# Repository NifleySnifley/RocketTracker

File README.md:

`stable-launch` - this is the most stable and recently updated version - work here

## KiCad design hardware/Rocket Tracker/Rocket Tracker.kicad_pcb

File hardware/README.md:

# Tracker

## Features:

- ESP32 SoC with WiFi and Bluetooth for downloading flight logs

- 8Mb log storage (about 104 minutes of logging)

- 3 I2C peripheral ports

- SMA Antenna port (or wire antenna)

- Voltage regulator supporting up to 7 cell LiPo (1-2 cell reccomended)

## Power useage

| Part        | Current useage min (mA) | Current useage max |
| ----------- | ----------------------- | ------------------ |
| ESP32-WROOM | 160                     | 260                |
| RFM97CW     | 120                     | 140                |
| FGPMMOPA6H  | 20                      | 25                 |

## Assembly:

1. ESP32-WROOM module

2. GPS

3. Qwiic (JST-SH) connectors

4. LEDs and respective resistors

5. RFM97

6. Voltage regulator

7. Capacitors

8. Programming headers

9. Antenna or SMA connector

**Alternate (fast) procedure:**

1. Reflow all components on the top (ESP32, GPS, etc.)

2. Solder the bottom SMD components with paste and hot air gun

3. Hand solder the radio and THT components

## BOM:

| Ref         | Qnty | Value               | Cmp name            | Footprint                                                  | Description                                                                                                                                                                   | Vendor                                                                                              |
| ----------- | ---- | ------------------- | ------------------- | ---------------------------------------------------------- | ----------------------------------------------------------------------------------------------------------------------------------------------------------------------------- | --------------------------------------------------------------------------------------------------- |
| C1, C3,     | 2    | 10uF                | C_Small             | Capacitor_SMD:C_1210_3225Metric_Pad1.33x2.70mm_HandSolder  | Unpolarized capacitor, small symbol                                                                                                                                           | Digikey                                                                                             |
| C2,         | 1    | .1uF                | C_Small             | Capacitor_SMD:C_0603_1608Metric_Pad1.08x0.95mm_HandSolder  | Unpolarized capacitor, small symbol                                                                                                                                           | Digikey                                                                                             |
| D1, D2,     | 2    | LED                 | LED                 | LED_SMD:LED_0603_1608Metric_Pad1.05x0.95mm_HandSolder      | Light emitting diode                                                                                                                                                          | Digikey                                                                                             |
| J1,         | 1    | Conn_02x03_Odd_Even | Conn_02x03_Odd_Even | Connector_PinHeader_1.27mm:PinHeader_2x03_P1.27mm_Vertical | Generic connector, double row, 02x03, odd/even pin numbering scheme (row 1 odd numbers, row 2 even numbers), script generated (kicad-library-utils/schlib/autogen/connector/) | Digikey                                                                                             |
| J2,         | 1    | Conn_02x05_Odd_Even | Conn_02x05_Odd_Even | Connector_PinHeader_1.27mm:PinHeader_2x05_P1.27mm_Vertical | Generic connector, double row, 02x05, odd/even pin numbering scheme (row 1 odd numbers, row 2 even numbers), script generated (kicad-library-utils/schlib/autogen/connector/) | Digikey                                                                                             |
| J4,         | 1    | Conn_Coaxial        | Conn_Coaxial        | Connector_Coaxial:SMA_Amphenol_132289_EdgeMount            | coaxial connector (BNC, SMA, SMB, SMC, Cinch/RCA, LEMO, ...)                                                                                                                  | Digikey                                                                                             |
| J5,         | 1    | Conn_01x02          | Conn_01x02          | Connector_PinHeader_2.54mm:PinHeader_1x02_P2.54mm_Vertical | Generic connector, single row, 01x02, script generated (kicad-library-utils/schlib/autogen/connector/)                                                                        | Digikey                                                                                             |
| J6, J7, J8, | 3    | Conn_01x04          | Conn_01x04          | Parts:Connector_Qwiic_Vertical                             | Generic connector, single row, 01x04, script generated (kicad-library-utils/schlib/autogen/connector/)                                                                        | Digikey                                                                                             |
| R1, R2,     | 2    | R_Small             | R_Small             | Resistor_SMD:R_0603_1608Metric_Pad0.98x0.95mm_HandSolder   | Resistor, small symbol                                                                                                                                                        | Digikey                                                                                             |
| U1,         | 1    | ESP32-WROOM-32      | ESP32-WROOM-32      | RF_Module:ESP32-WROOM-32                                   | RF Module, ESP32-D0WDQ6 SoC, Wi-Fi 802.11b/g/n, Bluetooth, BLE, 32-bit, 2.7-3.6V, onboard antenna, SMD                                                                        | [SparkFun](https://www.sparkfun.com/products/17830)                                                 |
| U2,         | 1    | RFM97CW-915S2       | RFM97CW-915S2       | RF_Module:HOPERF_RFM9XW_SMD                                | Low power long range transceiver module, SPI and parallel interface, 915 MHz, spreading factor 6 to12, bandwith 7.8 to 500kHz, -111 to -139 dBm, SMD-16, DIP-16               | [SparkFun](https://www.sparkfun.com/products/18084)                                                 |
| U3,         | 1    | FGPMMOPA6H          | FGPMMOPA6H          | Parts:FGPMMOPA6H                                           | "Adafruit Ultimate MTK3333 GPS"                                                                                                                                               | Adafruit, [Cheap Source](https://www.tinyosshop.com/index.php?route=product/product&product_id=840) |
| U5,         | 1    | LD1117V33           | LD1117V33           | Package_TO_SOT_SMD:TO-252-2                                | 1.5A 35V Adjustable Linear Regulator, TO-220                                                                                                                                  | Digikey                                                                                             |
| U4,         | 1    | BMI160              | BMI160              | Package_LGA:Bosch_LGA-14_3x2.5mm_P0.5mm                    | Small, low power inertial measurement unit, LGA-14                                                                                                                            | Chip Shortage                                                                                       |
| R3, R4,     | 2    | 10k                 | R_Small             | Resistor_SMD:R_0603_1608Metric_Pad0.98x0.95mm_HandSolder   | Resistor, small symbol                                                                                                                                                        | Digikey                                                                                             |

# Tracker (BaseStationHAT)

## BOM:

| Ref     | Qnty | Value                        | Cmp name                 | Footprint                                                  | Description                                                                                                                                                                   | Vendor                                              |
| ------- | ---- | ---------------------------- | ------------------------ | ---------------------------------------------------------- | ----------------------------------------------------------------------------------------------------------------------------------------------------------------------------- | --------------------------------------------------- |
| AE1,    | 1    | Antenna_Chip                 | Antenna_Chip             | RF_Antenna:Pulse_W3011                                     | Ceramic chip antenna with pin for PCB trace                                                                                                                                   | Digikey                                             |
| BT1,    | 1    | Battery_Cell                 | Battery_Cell             | Battery:BatteryHolder_Keystone_3000_1x12mm                 | Single-cell battery                                                                                                                                                           | [SparkFun](https://www.sparkfun.com/products/10592) |
| C1,     | 1    | 3.3pF                        | C_Small                  | Capacitor_SMD:C_0402_1005Metric_Pad0.74x0.62mm_HandSolder  | Unpolarized capacitor, small symbol                                                                                                                                           | Digikey                                             |
| C2,     | 1    | .1uF                         | C_Small                  | Capacitor_SMD:C_0603_1608Metric_Pad1.08x0.95mm_HandSolder  | Unpolarized capacitor, small symbol                                                                                                                                           | Digikey                                             |
| C3,     | 1    | 10uF                         | C_Small                  | Capacitor_SMD:C_1210_3225Metric_Pad1.33x2.70mm_HandSolder  | Unpolarized capacitor, small symbol                                                                                                                                           | Digikey                                             |
| J1,     | 1    | Screw_Terminal_01x02         | Screw_Terminal_01x02     | TerminalBlock:TerminalBlock_bornier-2_P5.08mm              | Generic screw terminal, single row, 01x02, script generated (kicad-library-utils/schlib/autogen/connector/)                                                                   | Digikey                                             |
| J2, J4, | 2    | Conn_Coaxial                 | Conn_Coaxial             | CONREVSMA003:LINX_CONREVSMA003.062                         | coaxial connector (BNC, SMA, SMB, SMC, Cinch/RCA, LEMO, ...)                                                                                                                  | Digikey                                             |
| J3,     | 1    | 40HAT                        | OX40HAT                  | Connector_PinSocket_2.54mm:PinSocket_2x20_P2.54mm_Vertical | 20x2 (40 pin) female pin socket, 2.54mm pitch (Raspberry pi receptacle)                                                                                                       | Anny supplier                                       |
| J5,     | 1    | Conn_02x06_Counter_Clockwise | Conn_02x06_Odd_Even      | Connector_PinHeader_2.54mm:PinHeader_2x06_P2.54mm_Vertical | Generic connector, double row, 02x06, odd/even pin numbering scheme (row 1 odd numbers, row 2 even numbers), script generated (kicad-library-utils/schlib/autogen/connector/) | Digikey                                             |
| J6,     | 1    | Conn_01x10                   | Conn_01x10               | Connector_PinHeader_2.54mm:PinHeader_1x10_P2.54mm_Vertical | Generic connector, single row, 01x10, script generated (kicad-library-utils/schlib/autogen/connector/)                                                                        | Digikey                                             |
| J7, J8, | 2    | Conn_01x04                   | Conn_01x04               | Parts:Connector_Qwiic_Vertical                             | Generic connector, single row, 01x04, scrhttps://www.sparkfun.com/products/16766ipt generated (kicad-library-utils/schlib/autogen/connector/)                                 | [SparkFun]()                                        |
| JP1,    | 1    | Jumper_3_Bridged12           | Jumper_3_Bridged12       | Connector_PinHeader_2.54mm:PinHeader_1x03_P2.54mm_Vertical | Jumper, 3-pole, pins 1+2 closed/bridged                                                                                                                                       | Digikey                                             |
| JP2,    | 1    | SolderJumper_3_Open          | SolderJumper_3_Open      | Jumper:SolderJumper-3_P1.3mm_Open_Pad1.0x1.5mm             | Solder Jumper, 3-pole, open                                                                                                                                                   | N/A                                                 |
| JP3,    | 1    | SolderJumper_3_Bridged12     | SolderJumper_3_Bridged12 | Jumper:SolderJumper-3_P1.3mm_Bridged12_Pad1.0x1.5mm        | 3-pole Solder Jumper, pins 1+2 closed/bridged                                                                                                                                 | N/A                                                 |
| R1,     | 1    | 1k                           | R_Small                  | Resistor_SMD:R_0603_1608Metric_Pad0.98x0.95mm_HandSolder   | Resistor, small symbol                                                                                                                                                        | Digikey                                             |
| R2,     | 1    | 10k                          | R_Small                  | Resistor_SMD:R_0603_1608Metric_Pad0.98x0.95mm_HandSolder   | Resistor, small symbol                                                                                                                                                        | Digikey                                             |
| U1,     | 1    | RFM97CW-915S2                | RFM97CW-915S2            | RF_Module:HOPERF_RFM9XW_SMD                                | Low power long range transceiver module, SPI and parallel interface, 915 MHz, spreading factor 6 to12, bandwith 7.8 to 500kHz, -111 to -139 dBm, SMD-16, DIP-16               | [SparkFun](https://www.sparkfun.com/products/18084) |
| U2,     | 1    | ATtiny414-SS                 | ATtiny414-SS             | Package_SO:SOIC-14_3.9x8.7mm_P1.27mm                       | 20MHz, 4kB Flash, 256B SRAM, 128B EEPROM, SOIC-14                                                                                                                             | Digikey                                             |
| U3,     | 1    | RFM69HCW                     | RFM69HCW                 | RF_Module:HOPERF_RFM69HW                                   | Low power ISM Radio Transceiver Module, SPI interface, AES encryption, 434 or 915 MHz, up to 100mW, up to 300 kb/s, SMD-16, DIP-16                                            | [SparkFun](https://www.sparkfun.com/products/13909) |
| U4,     | 1    | SL871L                       | SL871L                   | Parts:SL871                                                |                                                                                                                                                                               | Digikey                                             |
| U5,     | 1    | MCP23008                     | MCP23008                 | Package_DIP:DIP-18_W7.62mm_LongPads                        |                                                                                                                                                                               | Digikey                                             |
| U6,     | 1    | LD1117V33                    | LD1117V33                | Package_TO_SOT_SMD:TO-252-2                                | 1.5A 35V Adjustable Linear Regulator, TO-220                                                                                                                                  | Digikey                                             |

## Features:

- **ATtiny414 PRU**:
  
  - ****Programmed with Pi's UART0
  
  - All IO pins broken out
  
  - I2C connected to Pi's I2C1
  
  - Jumper for selecting UPDI (program mode) and VCC pullup for reset pin

- **RFM6X and RFM9X radio connections**:
  
  - Seperate CS and DIO0 connections to Pi allowing simultaneous operation
    
    - 9X: CS = GPIO18, DIO0 = GPIO27
    
    - 6X: CS = GPIO17, DIO0 = GPIO22
  
  - Shared reset pin
  
  - Individual antenna connections
    
    - edge-mount SMA/RP-SMA footprints

- **Telit SL871(L) GPS**:
  
  - NMEA Serial connected to UART3
  
  - I2C connected to I2C0
  
  - PulseLarsen chip antenna
  
  - Coin cell RTC battery
  
  - All important IO connected:
    
    - FORCEON: GPIO25
    
    - ANT_SC: GPIO23
    
    - ANT_OC: GPIO24
    
    - RESET: GPIO16
      
      - Note: must be pulled high or floating to enable GPS

- **MCP23008 GPIO Expander**:
  
  - All IO and power rail broken out to an easily accesible location on the board
  
  - Interfaced with I2C1 and interrupt pin connected to Pi's GPIO6

- **Screw terminals and voltage regulator for powering the Pi**:
  
  - Connected directly to the Pi's 5v rail and the 3.3v voltage regulator
  
  - **WARNING**: No reverse polarity or overvoltage protection provided, use at your own risk, and double check before connecting!

## Assembly:

It's reccomended to use solder paste and a hot air gun to solder the SMD components 

1. GPS (if applicable)

2. GPS antenna

3. Voltage regulator

4. ATtiny PRU

5. All SMD passives (pullups, caps)

6. Qwiic (I2C) connectors

7. Radio modules

8. (RP)SMA connectors (if applicable)

9. GPIO expander

10. Pin headers

11. HAT socket

12. Screw terminals

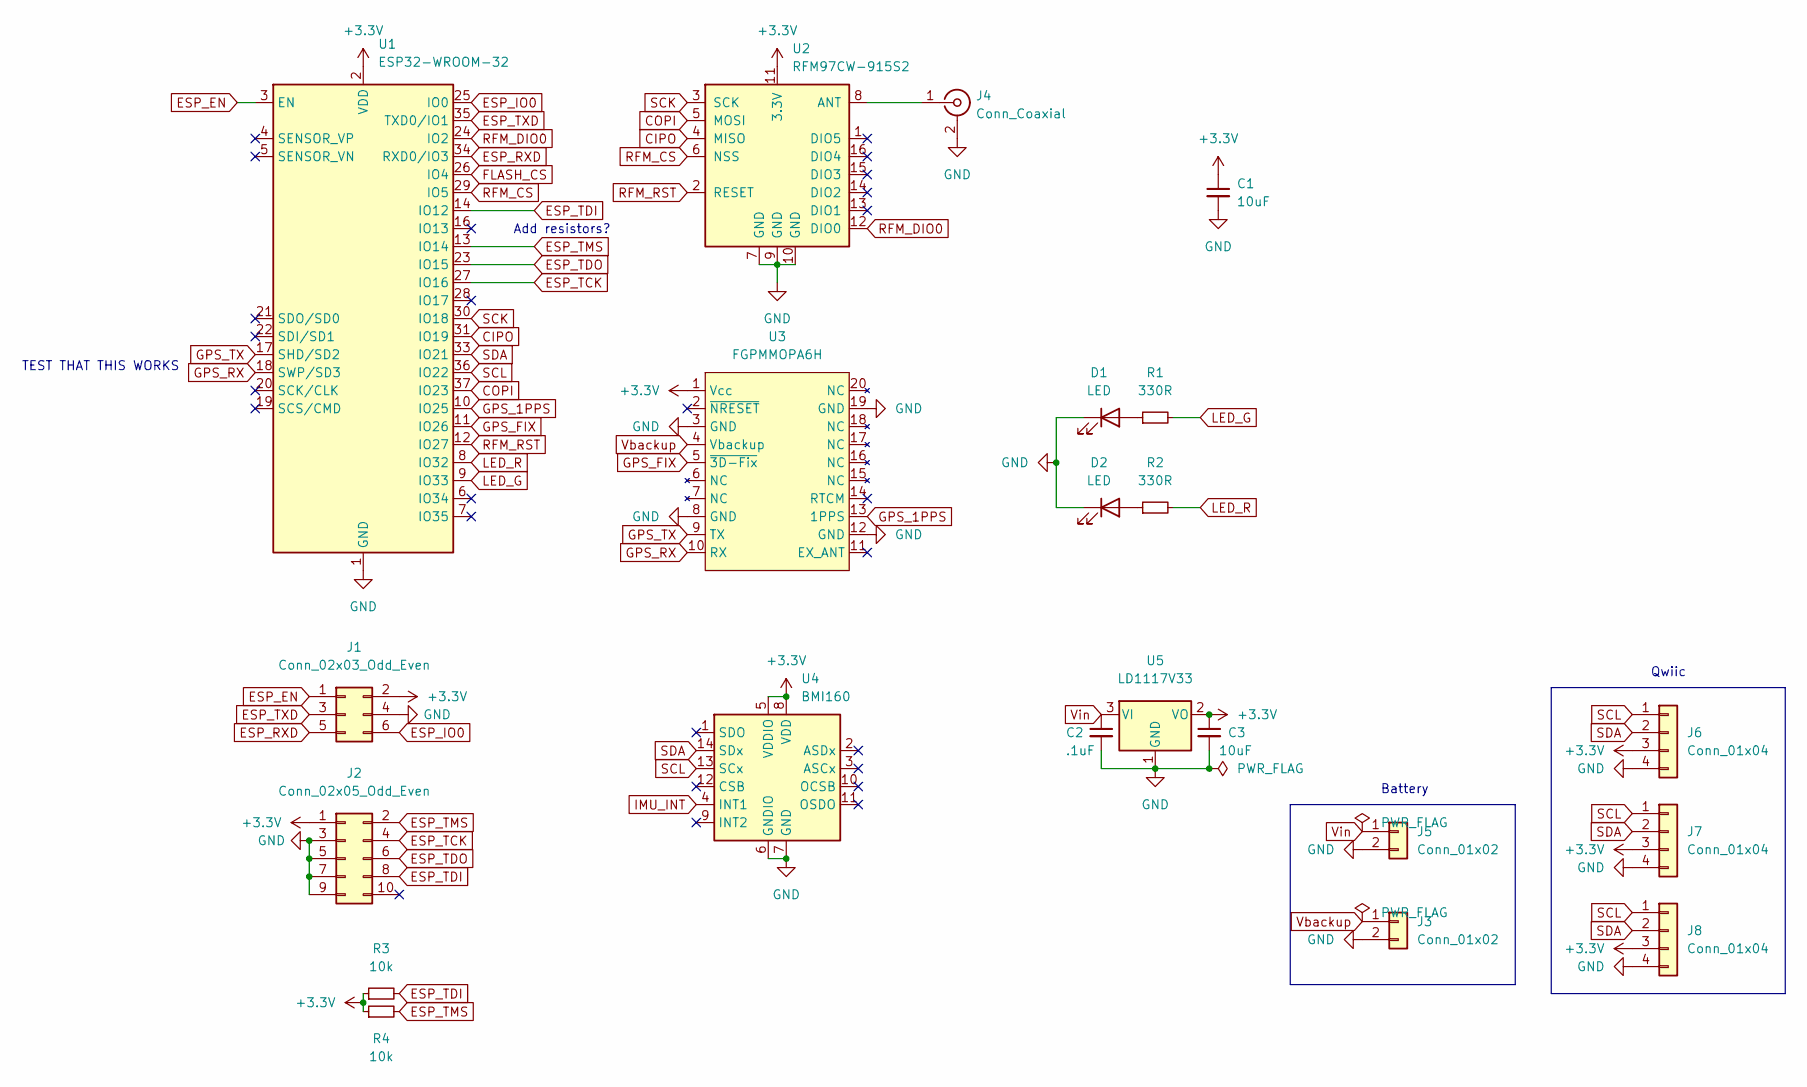
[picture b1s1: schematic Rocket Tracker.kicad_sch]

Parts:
C1, C3: 10uF; C_1210_3225Metric_Pad1.33x2.70mm_HandSolder
C2: .1uF; C_0603_1608Metric_Pad1.08x0.95mm_HandSolder
D1, D2: LED; LED_0603_1608Metric_Pad1.05x0.95mm_HandSolder
J1: Conn_02x03_Odd_Even; PinHeader_2x03_P1.27mm_Vertical
J2: Conn_02x05_Odd_Even; PinHeader_2x05_P1.27mm_Vertical
J3, J5: Conn_01x02; PinHeader_1x02_P2.54mm_Vertical
J4: Conn_Coaxial; LINX_CONREVSMA003.062
J6, J7, J8: Conn_01x04; Connector_Qwiic_Vertical
R1, R2: 330R; R_0603_1608Metric_Pad0.98x0.95mm_HandSolder
R3, R4: 10k; R_0603_1608Metric_Pad0.98x0.95mm_HandSolder
U1: ESP32-WROOM-32
U2: RFM97CW-915S2; HOPERF_RFM9XW_SMD
U3: FGPMMOPA6H
U4: BMI160; Bosch_LGA-14_3x2.5mm_P0.5mm
U5: LD1117V33; TO-252-2

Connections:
+3V3: C1.1, C3.1, J1.2, J2.1, J6.3, J7.3, J8.3, R3.1, R4.1, U1.2 (VDD), U2.11 (3.3V), U3.1 (Vcc), U4.5 (VDDIO), U4.8 (VDD), U5.2 (VO)
CIPO: U1.31 (IO19), U2.4 (MISO)
COPI: U1.37 (IO23), U2.5 (MOSI)
ESP_EN: J1.1, U1.3 (EN)
ESP_IO0: J1.6, U1.25 (IO0)
ESP_RXD: J1.5, U1.34 (RXD0/IO3)
ESP_TCK: J2.4, U1.27 (IO16)
ESP_TDI: J2.8, R3.2, U1.14 (IO12)
ESP_TDO: J2.6, U1.23 (IO15)
ESP_TMS: J2.2, R4.2, U1.13 (IO14)
ESP_TXD: J1.3, U1.35 (TXD0/IO1)
FLASH_CS: U1.26 (IO4)
GND: C1.2, C2.2, C3.2, D1.1 (K), D2.1 (K), J1.4, J2.3, J2.5, J2.7, J2.9, J3.2, J4.2 (Ext), J5.2, J6.4, J7.4, J8.4, U1.1 (GND), U1.15 (GND), U1.38 (GND), U1.39 (GND), U2.7 (GND), U2.9 (GND), U2.10 (GND), U3.3 (GND), U3.8 (GND), U3.12 (GND), U3.19 (GND), U4.6 (GNDIO), U4.7 (GND), U5.1 (GND)
GPS_1PPS: U1.10 (IO25), U3.13 (1PPS)
GPS_FIX: U1.11 (IO26), U3.5 (~3D-Fix)
GPS_RX: U1.18 (SWP/SD3), U3.10 (RX)
GPS_TX: U1.17 (SHD/SD2), U3.9 (TX)
IMU_INT: U4.4 (INT1)
LED_G: R1.2, U1.9 (IO33)
LED_R: R2.2, U1.8 (IO32)
unnamed: D1.2 (A), R1.1
unnamed: D2.2 (A), R2.1
unnamed: J4.1 (In), U2.8 (ANT)
RFM_CS: U1.29 (IO5), U2.6 (NSS)
RFM_DIO0: U1.24 (IO2), U2.12 (DIO0)
RFM_RST: U1.12 (IO27), U2.2 (RESET)
SCK: U1.30 (IO18), U2.3 (SCK)
SCL: J6.1, J7.1, J8.1, U1.36 (IO22), U4.13 (SCx)
SDA: J6.2, J7.2, J8.2, U1.33 (IO21), U4.14 (SDx)
Vbackup: J3.1, U3.4 (Vbackup)
Vin: C2.1, J5.1, U5.3 (VI)

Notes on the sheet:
TEST THAT THIS WORKS
Battery
Add resistors?
Qwiic

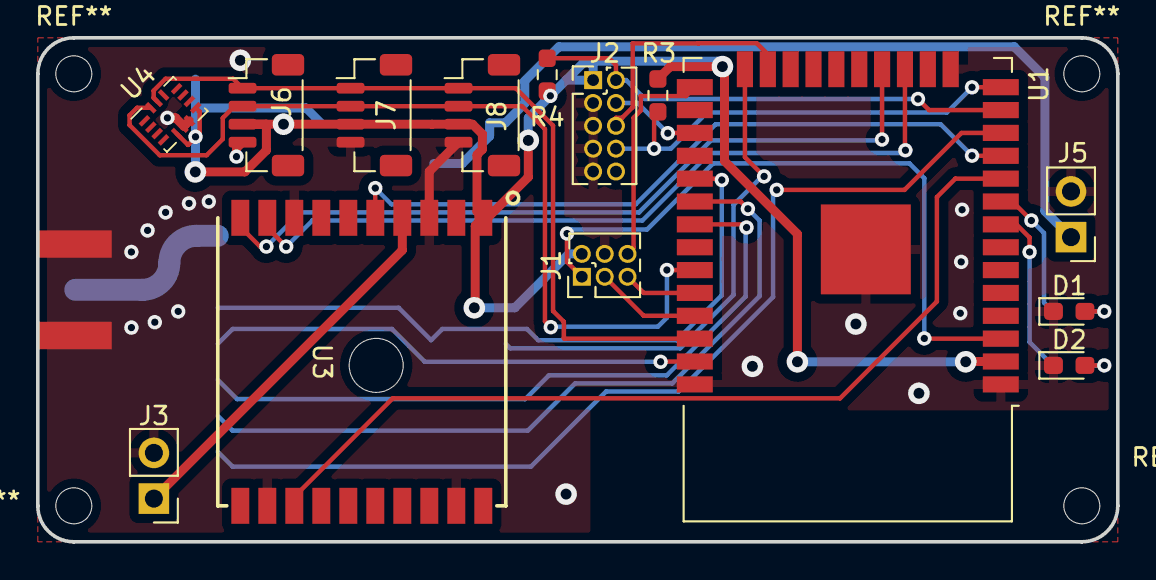
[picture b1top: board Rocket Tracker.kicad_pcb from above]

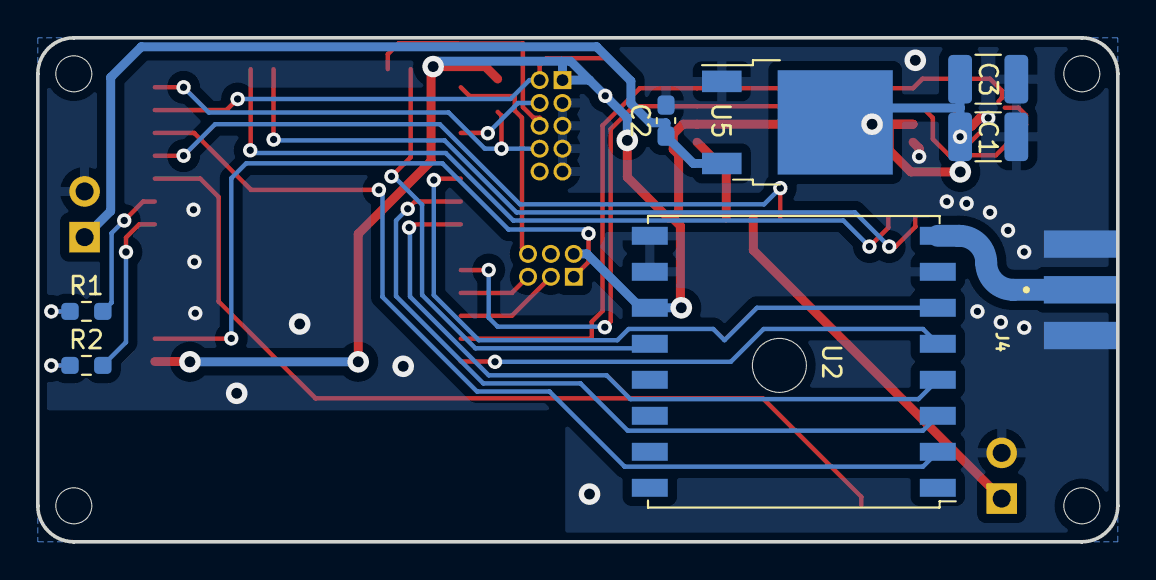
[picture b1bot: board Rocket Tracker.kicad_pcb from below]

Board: 2 copper layers, 60.0 x 28.0 mm, 22 parts (8 on the bottom side), 29 nets.

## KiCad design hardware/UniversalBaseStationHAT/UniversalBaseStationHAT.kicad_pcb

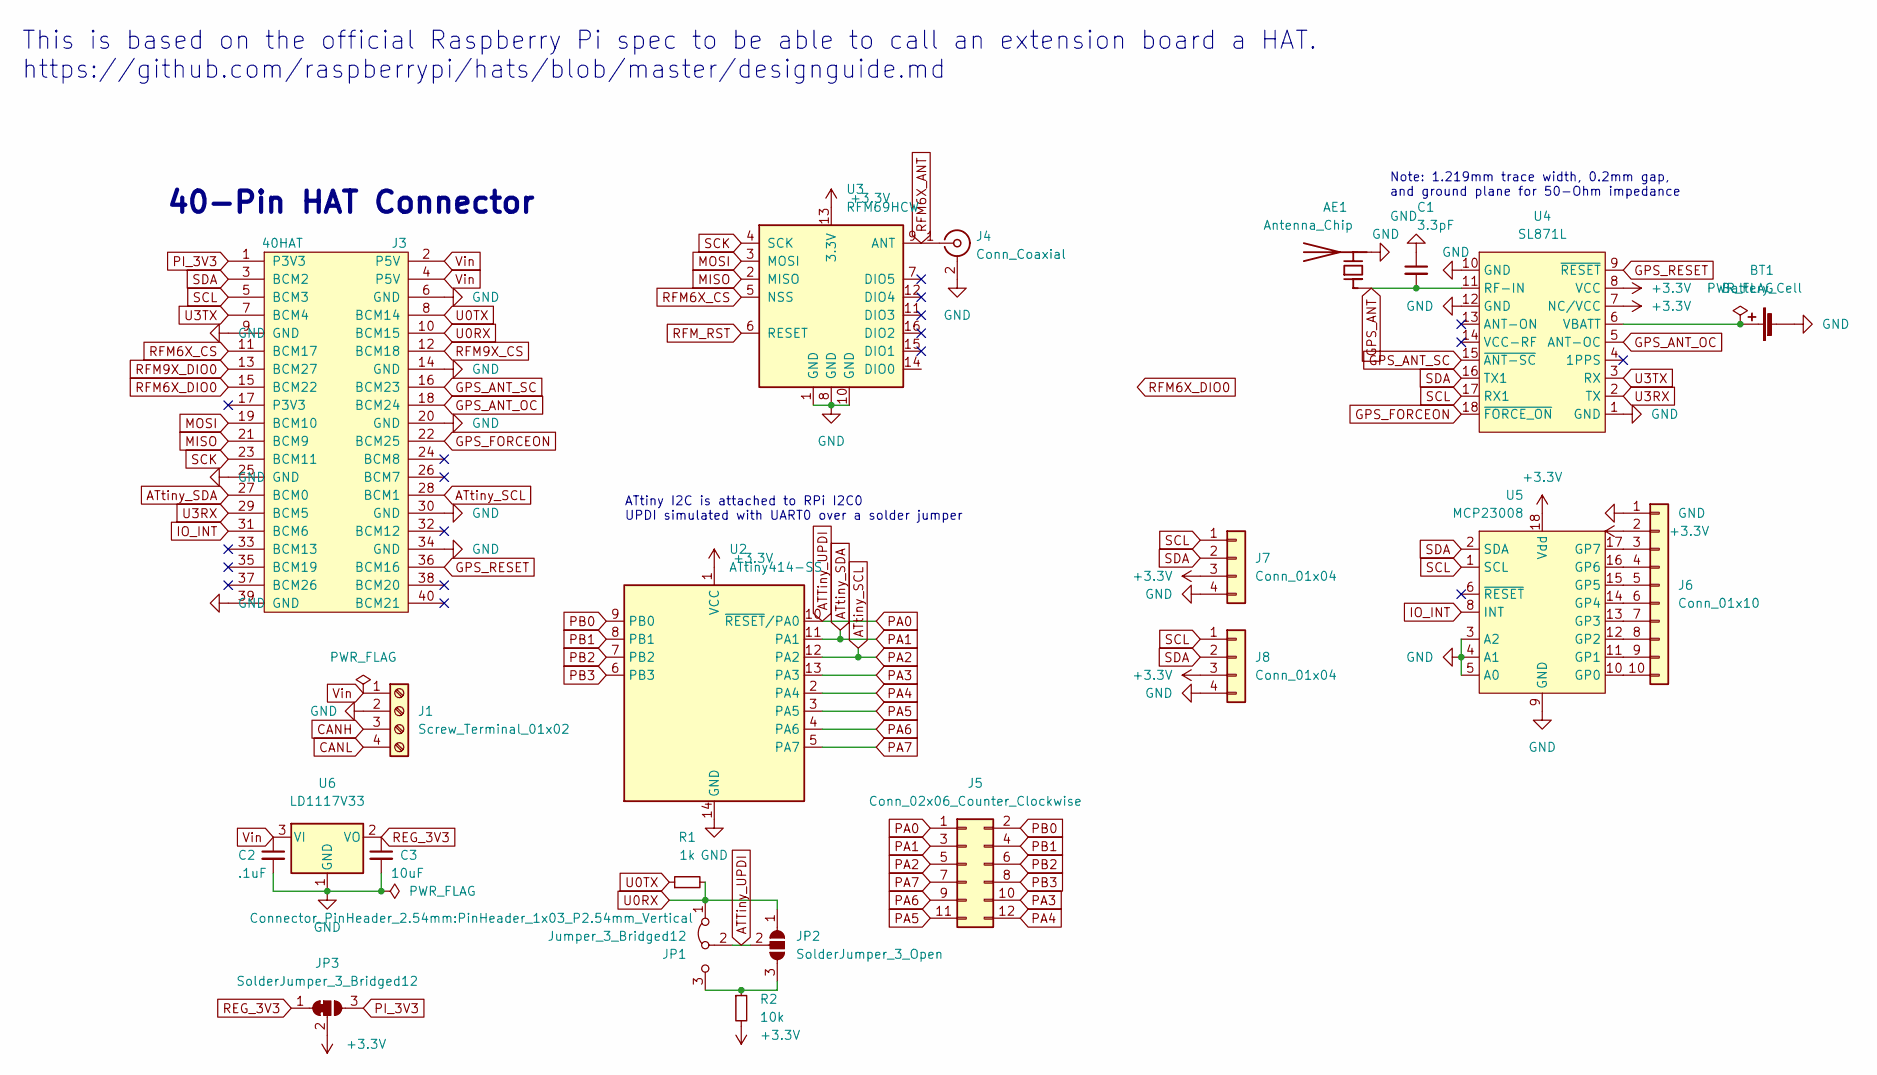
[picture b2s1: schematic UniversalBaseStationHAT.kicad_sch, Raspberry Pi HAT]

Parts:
AE1: Antenna_Chip; Pulse_W3011
BT1: Battery_Cell; BatteryHolder_Keystone_3000_1x12mm
C1: 3.3pF; C_0402_1005Metric_Pad0.74x0.62mm_HandSolder
C2: .1uF; C_0603_1608Metric_Pad1.08x0.95mm_HandSolder
C3: 10uF; C_1210_3225Metric_Pad1.33x2.70mm_HandSolder
J1: Screw_Terminal_01x02; TerminalBlock_bornier-4_P5.08mm
J3: 40HAT; PinSocket_2x20_P2.54mm_Vertical
J4: Conn_Coaxial; LINX_CONREVSMA003.062
J5: Conn_02x06_Counter_Clockwise; PinHeader_2x06_P2.54mm_Vertical
J6: Conn_01x10; PinHeader_1x10_P2.54mm_Vertical
J7, J8: Conn_01x04; Connector_Qwiic_Vertical
JP1: Jumper_3_Bridged12; PinHeader_1x03_P2.54mm_Vertical
JP2: SolderJumper_3_Open; SolderJumper-3_P1.3mm_Open_Pad1.0x1.5mm
JP3: SolderJumper_3_Bridged12; SolderJumper-3_P1.3mm_Bridged12_Pad1.0x1.5mm
R1: 1k; R_0603_1608Metric_Pad0.98x0.95mm_HandSolder
R2: 10k; R_0603_1608Metric_Pad0.98x0.95mm_HandSolder
U2: ATtiny414-SS; SOIC-14_3.9x8.7mm_P1.27mm
U3: RFM69HCW; HOPERF_RFM69HW
U4: SL871L; SL871
U5: MCP23008; DIP-18_W7.62mm_LongPads
U6: LD1117V33; TO-252-2

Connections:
+3V3: J6.2, J7.3, J8.3, JP3.2 (C), R2.2, U2.1 (VCC), U3.13 (3.3V), U4.7 (NC/VCC), U4.8 (VCC), U5.18 (Vdd)
ATTiny_UPDI: J5.1, JP1.2 (C), JP2.2 (C), U2.10 (~RESET/PA0)
ATtiny_SCL: J3.28 (BCM1), J5.5, U2.12 (PA2)
ATtiny_SDA: J3.27 (BCM0), J5.3, U2.11 (PA1)
CANH: J1.3
CANL: J1.4
GND: AE1.2 (PCB_Trace), BT1.2 (-), C1.1, C2.2, C3.2, J1.2, J3.6 (GND), J3.9 (GND), J3.14 (GND), J3.20 (GND), J3.25 (GND), J3.30 (GND), J3.34 (GND), J3.39 (GND), J4.2 (Ext), J6.1, J7.4, J8.4, U2.14 (GND), U3.1 (GND), U3.8 (GND), U3.10 (GND), U4.1 (GND), U4.10 (GND), U4.12 (GND), U5.3 (A2), U5.4 (A1), U5.5 (A0), U5.9 (GND), U6.1 (GND)
GPS_ANT: AE1.1 (FEED), C1.2, U4.11 (RF-IN)
GPS_ANT_OC: J3.18 (BCM24), U4.5 (ANT-OC)
GPS_ANT_SC: J3.16 (BCM23), U4.15 (~ANT-SC)
GPS_FORCEON: J3.22 (BCM25), U4.18 (~FORCE_ON)
GPS_RESET: J3.36 (BCM16), U4.9 (~RESET)
IO_INT: J3.31 (BCM6), U5.8 (INT)
MISO: J3.21 (BCM9), U3.2 (MISO)
MOSI: J3.19 (BCM10), U3.3 (MOSI)
unnamed: BT1.1 (+), U4.6 (VBATT)
unnamed: J6.3, U5.17 (GP7)
unnamed: J6.4, U5.16 (GP6)
unnamed: J6.5, U5.15 (GP5)
unnamed: J6.6, U5.14 (GP4)
unnamed: J6.7, U5.13 (GP3)
unnamed: J6.8, U5.12 (GP2)
unnamed: J6.9, U5.11 (GP1)
unnamed: J6.10, U5.10 (GP0)
unnamed: JP1.3 (B), JP2.3 (B), R2.1
PA3: J5.10, U2.13 (PA3)
PA4: J5.12, U2.2 (PA4)
PA5: J5.11, U2.3 (PA5)
PA6: J5.9, U2.4 (PA6)
PA7: J5.7, U2.5 (PA7)
PB0: J5.2, U2.9 (PB0)
PB1: J5.4, U2.8 (PB1)
PB2: J5.6, U2.7 (PB2)
PB3: J5.8, U2.6 (PB3)
PI_3V3: J3.1 (P3V3), JP3.3 (B)
REG_3V3: C3.1, JP3.1 (A), U6.2 (VO)
RFM6X_ANT: J4.1 (In), U3.9 (ANT)
RFM6X_CS: J3.11 (BCM17), U3.5 (NSS)
RFM6X_DIO0: J3.15 (BCM22)
RFM9X_CS: J3.12 (BCM18)
RFM9X_DIO0: J3.13 (BCM27)
RFM_RST: U3.6 (RESET)
SCK: J3.23 (BCM11), U3.4 (SCK)
SCL: J3.5 (BCM3), J7.1, J8.1, U4.17 (RX1), U5.1 (SCL)
SDA: J3.3 (BCM2), J7.2, J8.2, U4.16 (TX1), U5.2 (SDA)
U0RX: J3.10 (BCM15), JP1.1 (A), JP2.1 (A), R1.2
U0TX: J3.8 (BCM14), R1.1
U3RX: J3.29 (BCM5), U4.2 (TX)
U3TX: J3.7 (BCM4), U4.3 (RX)
Vin: C2.1, J1.1, J3.2 (P5V), J3.4 (P5V), U6.3 (VI)

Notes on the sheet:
This is based on the official Raspberry Pi spec to be able to call an extension board a HAT. https://github.com/raspberrypi/hats/blob/master/designguide.md
40-Pin HAT Connector
Note: 1.219mm trace width, 0.2mm gap, and ground plane for 50-Ohm impedance
ATtiny I2C is attached to RPi I2C0 UPDI simulated with UART0 over a solder jumper

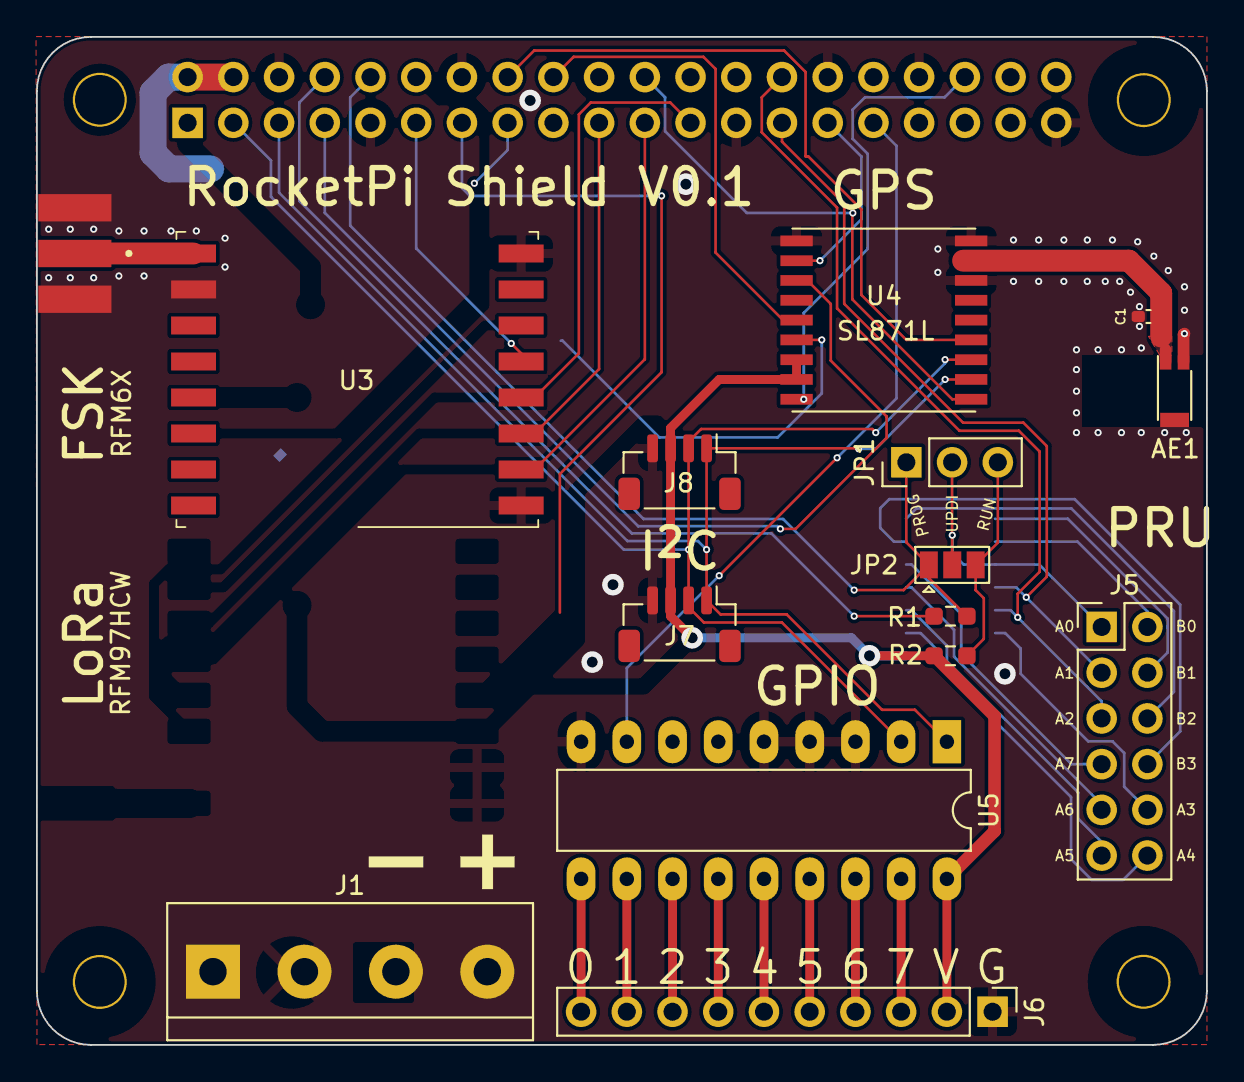
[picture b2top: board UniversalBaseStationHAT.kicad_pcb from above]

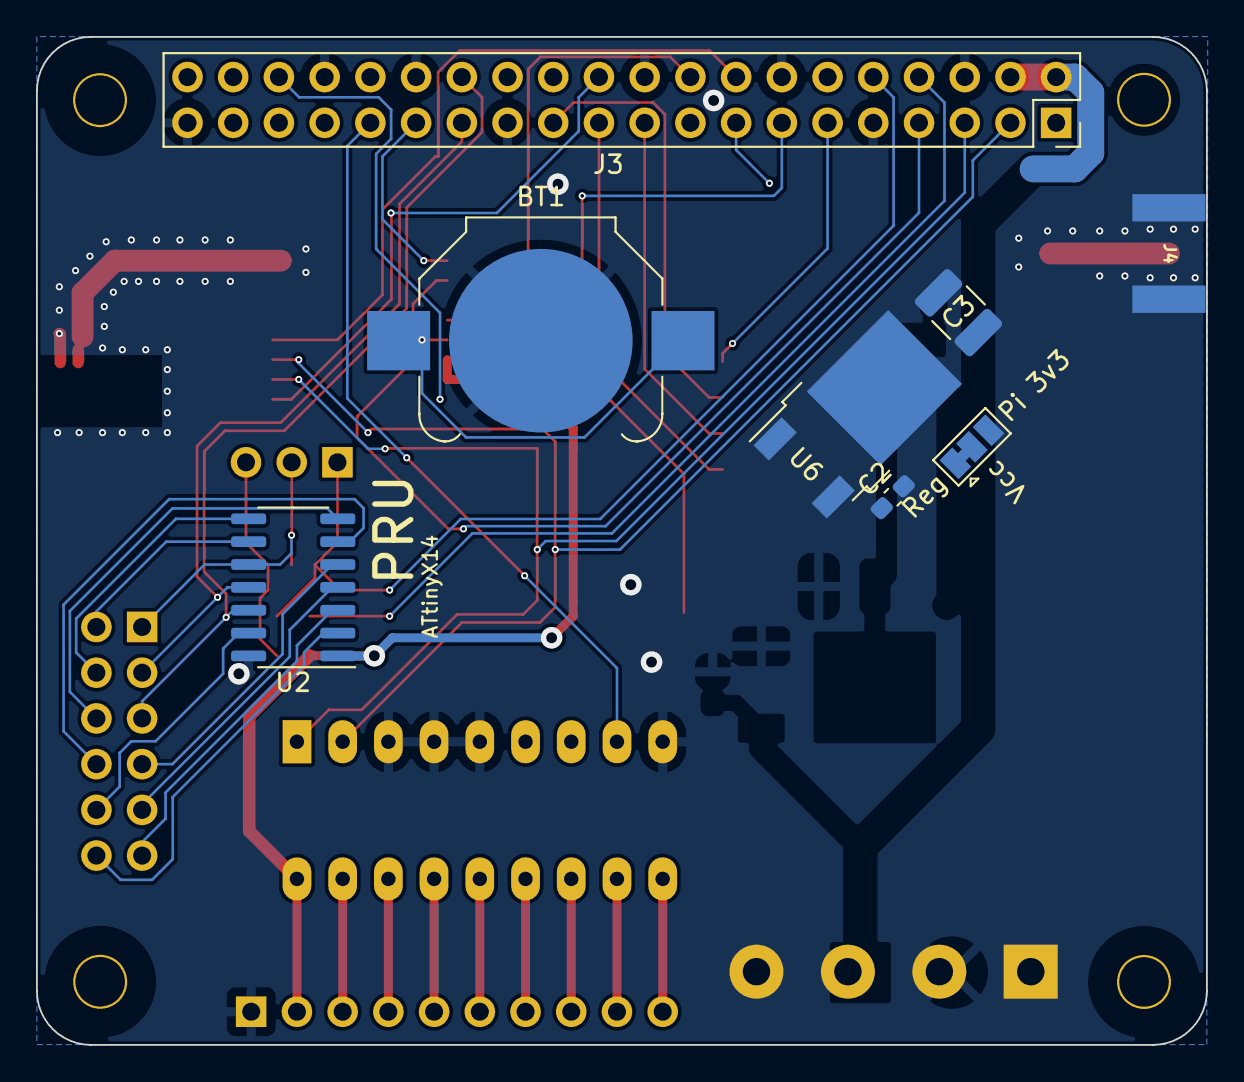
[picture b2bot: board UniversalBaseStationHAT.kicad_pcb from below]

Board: 2 copper layers, 65.0 x 56.0 mm, 26 parts (7 on the bottom side), 44 nets.

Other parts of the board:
H1, H2, H3, H4: 3mm_Mounting_Hole; NPTH_3mm_ID

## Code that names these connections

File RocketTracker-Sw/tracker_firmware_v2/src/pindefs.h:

// Pinout for U12 (ESP32-S3-WROOM-1)
#define PIN_EXP1 (gpio_num_t) 4
#define PIN_EXP2 (gpio_num_t) 5
#define PIN_EXP3 (gpio_num_t) 6
#define PIN_EXP4 (gpio_num_t) 7
#define PIN_LED_G (gpio_num_t) 15
#define PIN_LED_R (gpio_num_t) 16
#define PIN_GPS_SDI (gpio_num_t) 17
#define PIN_GPS_SDO (gpio_num_t) 18
#define PIN_USB_N (gpio_num_t) 19
#define PIN_USB_P (gpio_num_t) 20
#define PIN_ADXL_INT1 (gpio_num_t) 3
#define PIN_ADXL_CS (gpio_num_t) 9
#define PIN_LPS_CS (gpio_num_t) 10
#define PIN_MOSI (gpio_num_t) 11
#define PIN_SCK (gpio_num_t) 12
#define PIN_MISO (gpio_num_t) 13
#define PIN_LIS3MDL_CS (gpio_num_t) 14
#define PIN_LSM6DSM_CS (gpio_num_t) 21
#define PIN_ESP_BOOT (gpio_num_t) 0
#define PIN_RFM_RST (gpio_num_t) 35
#define PIN_RFM_D0 (gpio_num_t) 36
#define PIN_RFM_CS (gpio_num_t) 37
#define PIN_FLASH_CS (gpio_num_t) 38
#define PIN_TL_SCK (gpio_num_t) 39
#define PIN_TL_MOSI (gpio_num_t) 40
#define PIN_TL_MISO (gpio_num_t) 41
// #define PIN_NETNU12NRXD0 RXD0
// #define PIN_NETNU12NTXD0 TXD0
#define PIN_SCL (gpio_num_t) 2
#define PIN_SDA (gpio_num_t) 1

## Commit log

2022-06-29 Working cross-compilation and deployment to a Pi 4B
2022-06-29 Oopsie, restructured
2022-06-30 Basic compass support, its terrible though
2022-06-30 Configuration file, indev auto-calibration
2022-06-30 Fixed compass spinning, better GPS readout
2022-06-30 Improved compass rendering
2022-07-01 Working calibration, indev IMU
2022-07-01 Improved IMU reading
2022-07-19 Add template for tracker firmware
2022-07-20 Switched to PlatformIO and added protobufs
2022-07-21 Add more sophisticated transmission of data
2022-07-24 Tracker sending to seeker script with RFM97
2022-07-24 Added script to test radio receiving on seeker
2022-07-24 Transmission + reception seq. w/ modified RadioLib
2022-07-24 Modified test script with ack
2022-07-26 Better working radio transmissions
2022-07-26 Better receiver script
2022-07-27 Custom driver working for transmitting
2022-07-29 Fully operational driver
2022-07-30 Proper sending and configuration
2022-07-30 Copy files to redo seeker backend
2022-07-31 Fixed protobuf compilation and cleaned backend
2022-07-31 Template for frontend added and setup dev. env.
2022-07-31 Added font awesome icons
2022-08-01 Created (problably) worlds worst UI panel layout..
2022-08-04 WIP Adapters (traits) and README TODOs
2022-08-05 Added tungstenite websocket boilerplate.
2022-08-05 Basic amenities for event relaying
2022-08-06 Added map boilerplate, maptiler
2022-08-06 Satellite maps (basic)
2022-08-06 Improved adjustable grid layout
2022-08-07 Grid fixes, Websockets, etc.
2022-08-13 Added offline proxy
2022-08-13 JS Changes
2022-08-13 All fixed up (aside from the cache)
2022-08-14 Basic REST API (no functionality)
2022-08-22 WIP everything, did some work on backend
2023-04-13 Woah there! Started everything over. Added PCBs.
2023-04-13 I'm dumb, made PCBs submod and added SW dir
2023-07-30 Stuff, commit because commit
2023-08-16 Basic firmware for testing receiver, protocol infrastructure, forgot to commit
2023-08-18 Protocol things, DMA based asyncrhonous radio driver upgrades.
2023-08-19 Basic TinyUSB CDC ports, reset, etc.
2023-08-20 Emulated NMEA GPS for received messages, fixed driver
2023-08-21 Radio configuration via NMEA custom messages
2023-08-21 Minimal but "feature-complete" receiver firmware. Needs more extensive testing
2023-08-22 Remove debug messages from receiver firmware VGPS
2023-08-23 Working (basic) GPS tracking firmware!
2023-08-23 Restructure receiver for shared comms, radio rx status
2023-08-27 More work on stuff, PC software mostly
2023-08-27 Fix protobufs
2023-08-27 Escaping for raw message tx/rx
2023-08-28 Fixes for configuration of receiver w/ NMEA. No more CR config
2023-08-28 Operational GPS display on map!
2023-08-28 Builds with pyinstaller
2023-09-01 Stuff works?!?!?!
2023-09-01 Major additions to software, tweaked receiver
2023-09-01 Log analysis for basestation software
2023-09-01 Fixed proxy for Windows and requirements.txt
2023-09-05 Software improvements, bugfixes
2023-09-06 CRC check in framemanager for extra safety
2023-09-06 Fixes for CRC
2023-09-06 CRC supporting tracker firmware
2023-09-07 Barometric altitude in tracker firmware from LPS25
2023-09-07 Altitude graphs!
2023-09-07 Overall, software works! Could use some improvements to be viable for 100% duty cycle (serial thread, etc.) but oherwise it's OK
2023-09-08 Rapid, high duty-cycle transmission for better altitude update rate.
2024-07-04 3 Sensors Working for firmware v3
2024-07-04 Daily commit
2024-07-05 Functional tracking
2024-07-06 Update protocol
2024-07-06 Minor frame_manager fix (struct packing)
2024-07-06 Fixes to software & frame manager, needs merge
2024-07-07 Protocol implementation improvements
2024-07-07 Proto fixes
2024-07-07 Receiver fixes for new protocols
2024-07-08 Scripts for testing
2024-07-08 Logging, pings
2024-07-09 CLI, prototype log downloading (NEEDS TESTING)
2024-07-09 Log downloading. LIS3MDL is behaving badly...
2024-07-10 ADXL375 driver
2024-07-10 Bugfixes
2024-07-10 Receiver improvement to reduce packet loss & lockups
2024-07-11 Appears to be stable enough for the launch.
2024-07-11 Hw update
2024-07-11 Tiny Rx tweak
2024-07-11 Stable
2024-07-11 Receiver stability fixes.
2024-07-11 Fix python3.12 compatibility, ignore RSSI
2024-07-12 Critical fix: GPS lon overriden by altitude!
2024-07-16 PROGRESS
2024-07-16 GUI receiving.
2024-07-17 stuff
2024-07-23 Asio final commit
2024-07-25 Git stuff
2024-07-25 Configuration, calibration in firmware
2024-07-25 Fix stuff?
2024-07-25 minor fixes
2024-07-25 Ignore pycache
2024-07-29 Debug data over USB, fusion.
2024-07-29 Prelogging
2024-07-29 Filter commit
2024-07-29 Tuned filter
2024-07-30 Logger upgrades
2024-08-04 GPS Update! CLI Config save/load
2024-08-04 Actually using config values now!
2024-08-04 Log manipulation, fixes, etc.
2024-08-04 Log events, GPX export
2024-08-05 RX Fixes
2024-08-06 Link LoRa improvements, rebooting, etc.
2024-08-06 Minor RX fix
2024-08-06 Tweaks, whatever
2024-08-07 Misc features, mostly CLI oriented
2024-08-08 Add requirements for CLI
2024-08-08 Sensor disabling, and "recovery" from sensor init failure.
2024-08-08 CLI improvements
2024-08-09 TCP WIP Commit
2024-08-09 TCP Working from a tracker POV
2024-08-09 Work on TCP-failing
2024-08-10 CLI Tweak, fix log download temporarily
2024-08-16 Some launch-day tweaks and log analysis
2024-08-17 DDIO Beginnings, ESP_LOGx -> Log memory.
2024-08-19 DD sorta
2024-08-19 Not working pwm
2024-08-20 Temp commit
2024-08-20 Rudimentary HW support for the operational hardware parts of the DD board.
2024-08-20 Removed PWM & Fixed other stuff
2024-08-26 Fix tracker firmware build on linux
